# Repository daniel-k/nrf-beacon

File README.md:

nrf-beacon
==========

Please do

```bash
git submodule init
git submodule update
```

after cloning to fetch the xpcc library

Build and program via DFU:

```bash
cd src/
scons dfu
```

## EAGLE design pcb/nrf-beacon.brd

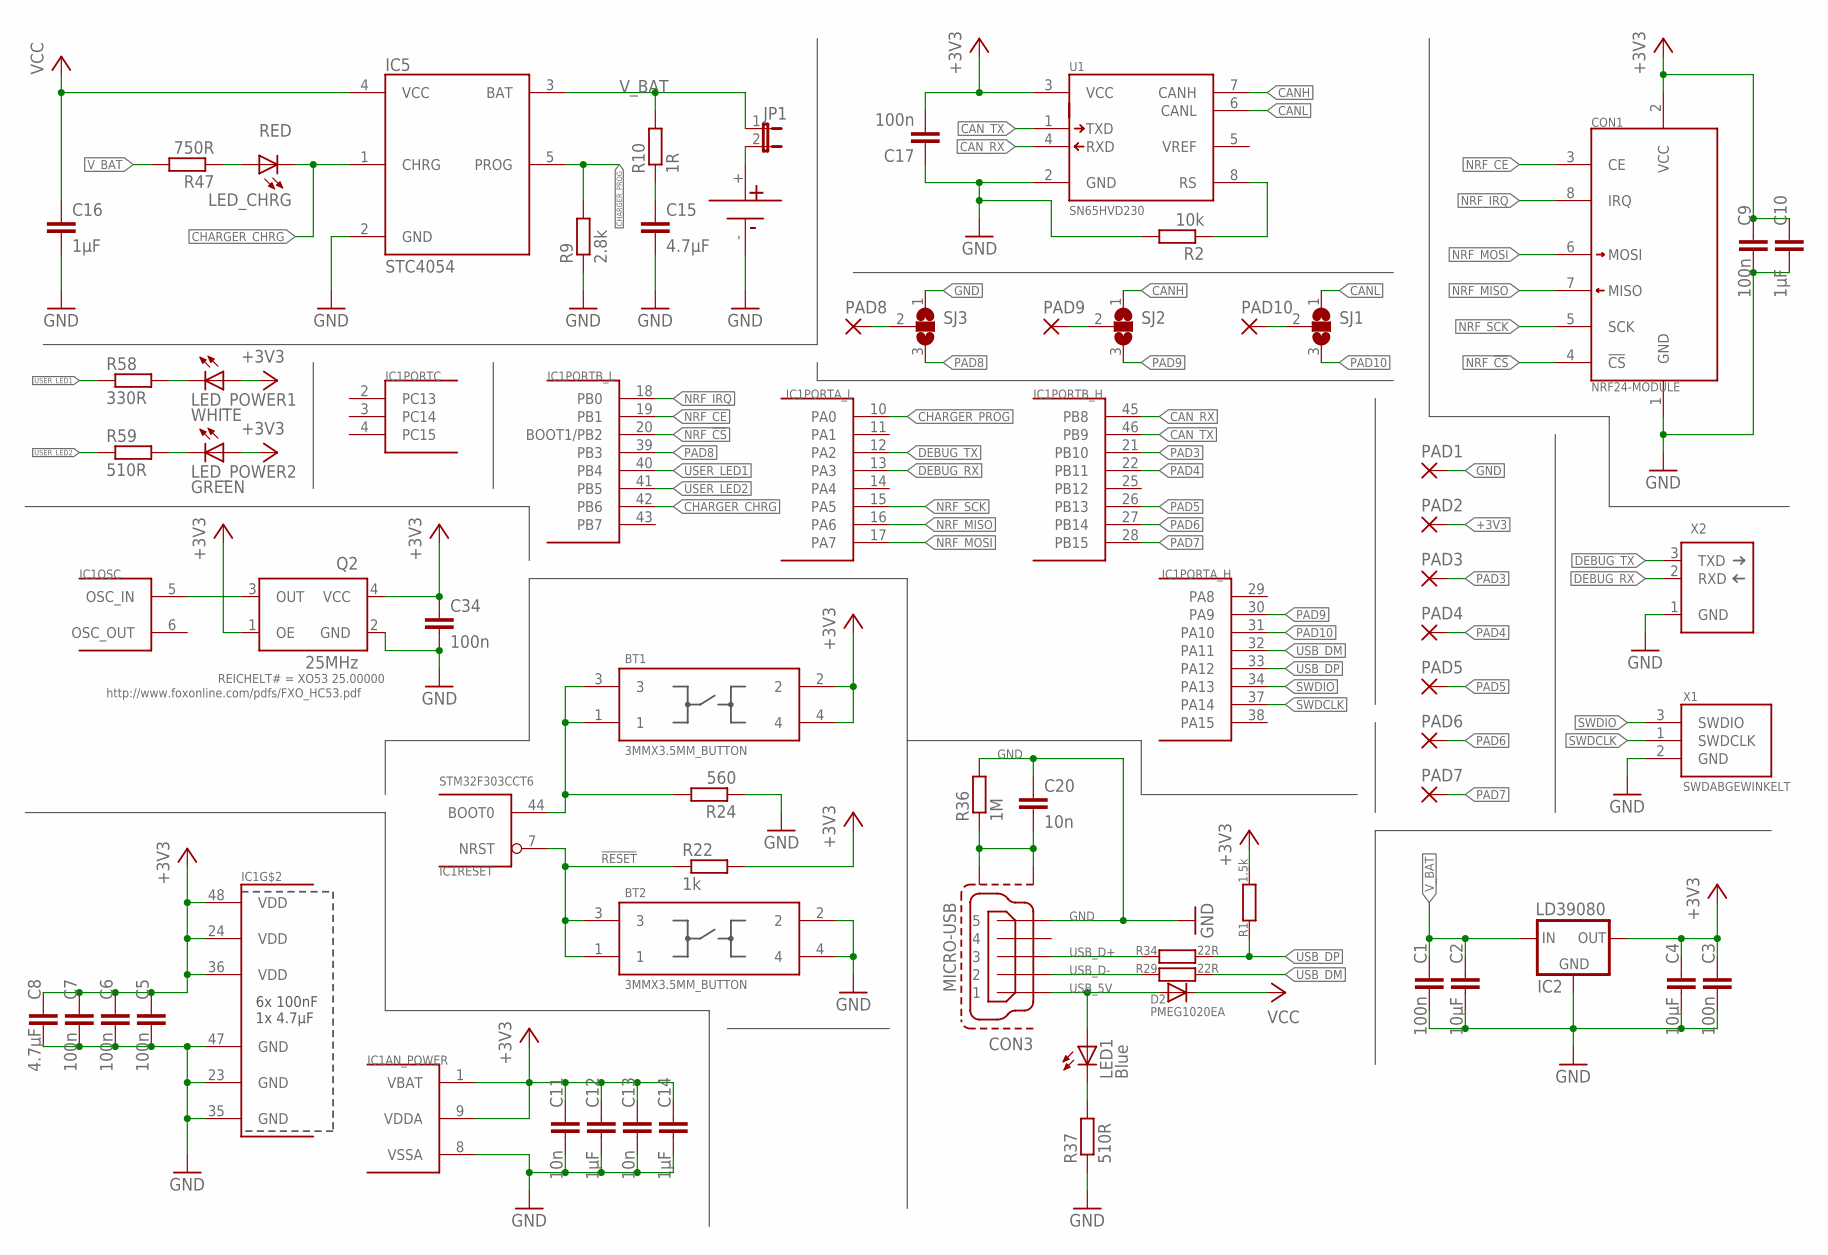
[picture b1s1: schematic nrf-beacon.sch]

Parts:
BT1, BT2: 3MMX3.5MM_BUTTON
C1, C3, C17: 100n; C1206
C2, C4: 10µF; C1206
C5, C6, C7, C9, C34: 100n; C0603
C8, C15: 4.7µF; C0603
C10, C12, C14, C16: 1µF; C0603
C11, C13: 10n; C0603
C20: 10n; C0805
CON1: NRF24-MODULE
CON3: MICRO-USB
D2: PMEG1020EA; SOD323-W
IC1: STM32F303CCT6; TQFP48
IC2: LD39080; DPAK
IC5: STC4054; SOT23-5L
JP1: JP1E; JP1
LED1: Blue; CHIPLED_0805
LED_CHRG: RED; CHIPLED_0805
LED_POWER1: WHITE; CHIPLED_0805
LED_POWER2: GREEN; CHIPLED_0805
PAD1, PAD2, PAD3, PAD4, PAD5, PAD6, PAD7, PAD8, PAD9, PAD10: WIREPADSMD5-1,8; 5-1,8
Q2: 25MHz; XO53
R1: 1.5k; M0805
R2: 10k; R0805
R9: 2.8k; R0603
R10: 1R; R0805
R22: 1k; R0603
R24: 560; R0805
R29, R34: 22R; M0805
R36: 1M; M0805
R37: 510R; M0805
R47: 750R; R0603; DIGIKEY# RMCF0805JT820RCT-ND
R58: 330R; R0603; DIGIKEY# 311-560GRCT-ND
R59: 510R; R0603; DIGIKEY# 311-560GRCT-ND
SJ1, SJ2, SJ3: SJ2W; SJ_2
U1: SN65HVD230; SOIC-8
U$1: BAT
X1: SWDABGEWINKELT; 7395-03
X2: SERIAL_DEBUG_3PINL; 7395-03

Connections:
!RESET: BT2.1, BT2.3, IC1.7 (NRST), R22.1
$234: PAD10.1, SJ1.2
$6757: PAD8.1, SJ3.2
+3V3: BT1.2, BT1.4, C3.1, C4.1, C5.1, C6.1, C7.1, C8.1, C9.1, C10.1, C11.1, C12.1, C13.1, C14.1, C17.2, C34.1, CON1.2 (VCC), IC1.1 (VBAT), IC1.9 (VDDA), IC1.24 (VDD), IC1.36 (VDD), IC1.48 (VDD), IC2.3 (OUT), LED_POWER1.A, LED_POWER2.A, PAD2.1, Q2.1 (OE), Q2.4 (VCC), R1.1, R22.2, U1.3 (VCC)
CANH: SJ2.1, U1.7 (CANH)
CANL: SJ1.1, U1.6 (CANL)
CAN_RX: IC1.45 (PB8), U1.4 (RXD)
CAN_TX: IC1.46 (PB9), U1.1 (TXD)
CHARGER_CHRG: IC1.42 (PB6), IC5.1 (CHRG), LED_CHRG.C
CHARGER_PROG: IC1.10 (PA0), IC5.5 (PROG), R9.2
DEBUG_RX: IC1.13 (PA3), X2.2 (RXD)
DEBUG_TX: IC1.12 (PA2), X2.3 (TXD)
GND: BT2.2, BT2.4, C1.2, C2.2, C3.2, C4.2, C5.2, C6.2, C7.2, C8.2, C9.2, C10.2, C11.2, C12.2, C13.2, C14.2, C15.2, C16.2, C17.1, C20.1, C34.2, CON1.1 (GND), CON3.5, IC1.8 (VSSA), IC1.23 (GND), IC1.35 (GND), IC1.47 (GND), IC2.2 (GND), IC5.2 (GND), PAD1.1, Q2.2 (GND), R2.2, R9.1, R24.1, R36.2, R37.1, SJ3.1, U1.2 (GND), U$1.-, X1.2 (GND), X2.1 (GND)
unnamed: JP1.2, U$1.+
unnamed: BT1.1, BT1.3, IC1.44 (BOOT0), R24.2
unnamed: R2.1, U1.8 (RS)
unnamed: PAD9.1, SJ2.2
unnamed: C20.2, CON3.SHIELDING1, CON3.SHIELDING2, R36.1
unnamed: LED1.C, R37.2
unnamed: C15.1, R10.1
unnamed: LED_POWER1.C, R58.2
unnamed: LED_CHRG.A, R47.1
unnamed: IC1.5 (OSC_IN), Q2.3 (OUT)
unnamed: LED_POWER2.C, R59.2
NRF_!CS: CON1.4 (!CS), IC1.20 (BOOT1/PB2)
NRF_CE: CON1.3 (CE), IC1.19 (PB1)
NRF_IRQ: CON1.8 (IRQ), IC1.18 (PB0)
NRF_MISO: CON1.7 (MISO), IC1.16 (PA6)
NRF_MOSI: CON1.6 (MOSI), IC1.17 (PA7)
NRF_SCK: CON1.5 (SCK), IC1.15 (PA5)
PAD3: IC1.21 (PB10), PAD3.1
PAD4: IC1.22 (PB11), PAD4.1
PAD5: IC1.26 (PB13), PAD5.1
PAD6: IC1.27 (PB14), PAD6.1
PAD7: IC1.28 (PB15), PAD7.1
PAD8: IC1.39 (PB3), SJ3.3
PAD9: IC1.30 (PA9), SJ2.3
PAD10: IC1.31 (PA10), SJ1.3
SWDCLK: IC1.37 (PA14), X1.1 (SWDCLK)
SWDIO: IC1.34 (PA13), X1.3 (SWDIO)
USB_5V: CON3.1, D2.A, LED1.A
USB_D+: CON3.3, R34.2
USB_D-: CON3.2, R29.2
USB_DM: IC1.32 (PA11), R29.1
USB_DP: IC1.33 (PA12), R1.2, R34.1
USER_LED1: IC1.40 (PB4), R58.1
USER_LED2: IC1.41 (PB5), R59.1
VCC: C16.1, D2.C, IC5.4 (VCC)
V_BAT: C1.1, C2.1, IC2.1 (IN), IC5.3 (BAT), JP1.1, R10.2, R47.2

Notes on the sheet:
http://www.foxonline.com/pdfs/FXO_HC53.pdf

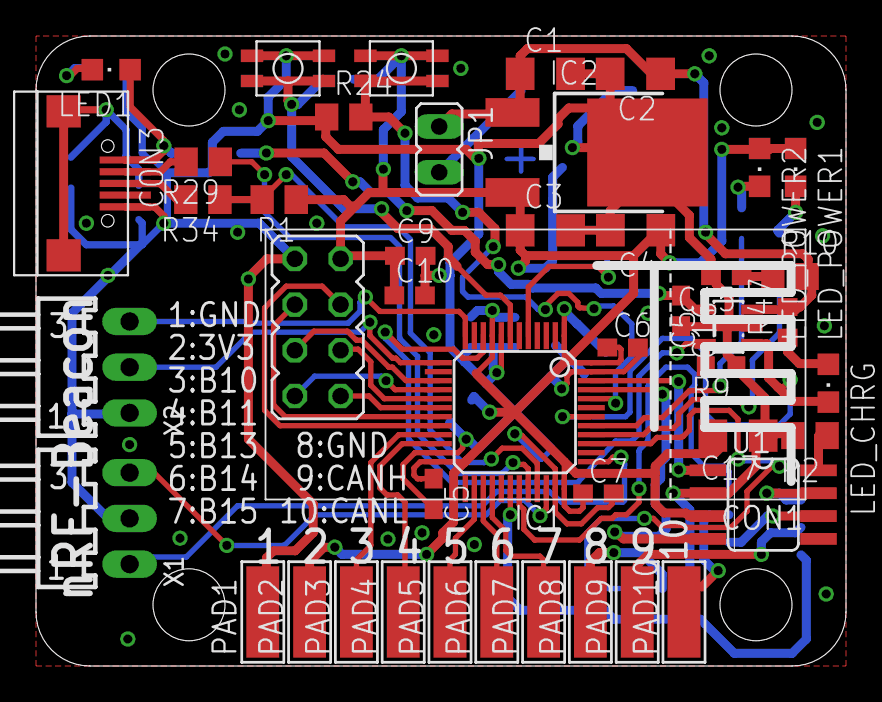
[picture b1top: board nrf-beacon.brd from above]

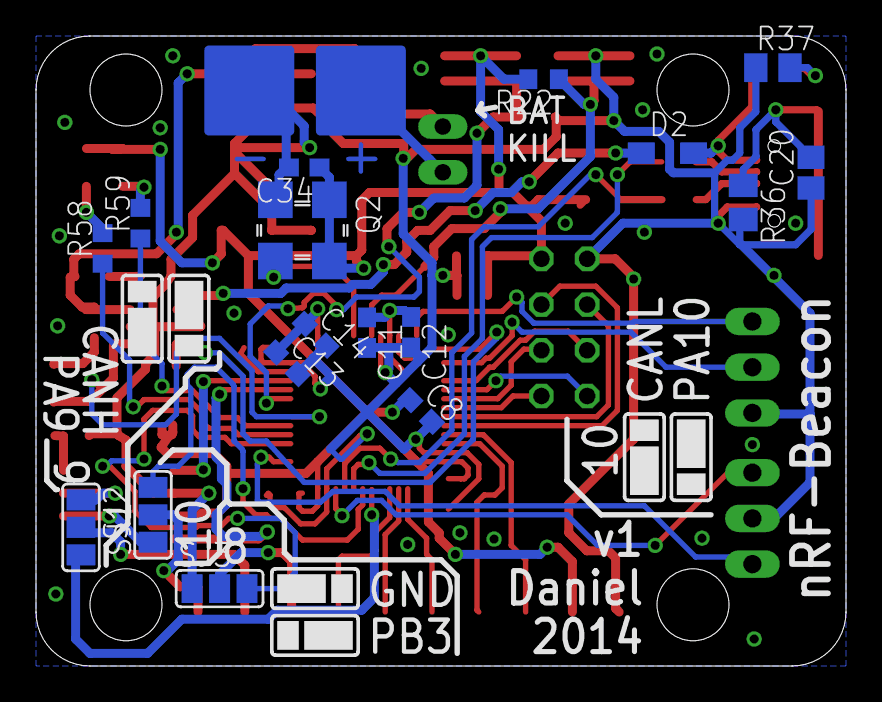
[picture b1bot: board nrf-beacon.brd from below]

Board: 2 copper layers, 45.0 x 35.0 mm, 63 parts (18 on the bottom side), 49 nets.

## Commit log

2014-09-20 put scons build scripts into src/
2014-09-20 add readme
2014-09-20 add hardware class
2014-09-20 refactor more into hardware class
2014-09-20 add pcb
2014-09-22 add license file
2014-09-22 update readme to better suit github markdown
2014-09-28 distinguish between boards by stm32's unique id
2014-09-28 tabs to spaces (width: 4)
2014-09-28 use xpcc's new parameter feature for setting uart tx buffer size
2014-09-30 read raw analog values of analog stick
2014-09-30 beautify console output and increase sampling time
2014-10-28 play around with picocomm and left stick, yolo
2014-10-29 pcb: add forgotten signal for monitoring charger
2014-12-19 led green and white was swapped
2014-12-22 update to new xpcc version (includes driver changes) and implement little test setup of phy layer.
2015-02-13 initialize Ce pin
2015-02-13 change module ids
2015-02-13 adapt to xpcc changes
2015-02-13 show retransmit count
2015-02-16 programming via local gdb session: $ openocd -f openocd.cfg $ # other terminal $ scons remote-program
2015-02-16 testing of new data layer (xpcc update later)
2015-02-18 use new xpcc version with recent nrf24 changes
2015-02-18 SConstruct: convert xpcc path to absolute path, needed for symlinked xpcc instead of submodule for now
2015-02-18 strip data-layer example and convert spaces to tabs
2015-02-26 adapt for new xpcc changes (xpcc submodule update pending)
2015-03-12 Add more debug and set destination address of packet.
2015-03-12 Simple reliability test.
2015-03-13 Reduce SPI frequency for debugging. Unclear if this caused problems.
2015-03-13 wip: Sample app that should test all channels between two stations.
2015-03-13 Make communication more robust and channel sensing actually work
2015-03-13 Silence output
2015-03-14 Implement text interface for statistics
2015-03-14 Beautify
